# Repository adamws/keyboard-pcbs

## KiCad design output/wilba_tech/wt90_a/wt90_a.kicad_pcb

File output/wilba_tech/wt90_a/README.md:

## wilba_tech/wt90_a

[layout](wt90_a-kle.json) - [PCB](wt90_a.kicad_pcb)

{:loading="lazy"}

[Open in keyboard-layout-editor](http://www.keyboard-layout-editor.com/##@@_c=#777777;&=0,0&_x:0.25&c=#cccccc;&=0,1&=0,2&=0,3&=0,4&_x:0.25&c=#aaaaaa;&=0,5&=0,6&=0,7&=0,8&_x:0.25&c=#cccccc;&=0,9&=0,10&=0,11&=0,12&_x:0.25&c=#aaaaaa;&=0,13&_x:0.5;&=0,14&=0,15&=0,16&=0,17;&@_y:0.25&c=#cccccc;&=1,0&=1,1&=1,2&=1,3&=1,4&=1,5&=1,6&=1,7&=1,8&=1,9&=1,10&=1,11&=1,12&_c=#aaaaaa&w:2;&=1,13&_x:0.5;&=1,14&=1,15&=1,16&=1,17;&@_w:1.5;&=2,0&_c=#cccccc;&=2,1&=2,2&=2,3&=2,4&=2,5&=2,6&=2,7&=2,8&=2,9&=2,10&=2,11&=2,12&_w:1.5;&=2,13&_x:0.5;&=2,14&=2,15&=2,16&_c=#aaaaaa;&=2,17;&@_w:1.75;&=3,0&_c=#cccccc;&=3,1&=3,2&=3,3&=3,4&=3,5&=3,6&=3,7&=3,8&=3,9&=3,10&=3,11&_c=#777777&w:2.25;&=3,12&_x:0.5&c=#cccccc;&=3,14&=3,15&=3,16&_c=#aaaaaa;&=3,17;&@_w:2.25;&=4,0&_c=#cccccc;&=4,2&=4,3&=4,4&=4,5&=4,6&=4,7&=4,8&=4,9&=4,10&=4,11&_c=#aaaaaa&w:1.75;&=4,12&_x:1.5&c=#cccccc;&=4,14&=4,15&=4,16&_c=#777777&h:2;&=4,17;&@_x:14.25&y:-0.75&c=#cccccc;&=4,13;&@_y:-0.25&c=#aaaaaa&w:1.5;&=5,0&_w:1.5;&=5,1&_c=#cccccc&w:7;&=5,6&_c=#aaaaaa&w:1.5;&=5,10&_w:1.5;&=5,11&_x:3.5&c=#cccccc;&=5,15&=5,16;&@_x:13.25&y:-0.75;&=5,12&=5,13&=5,14)

{:loading="lazy"}

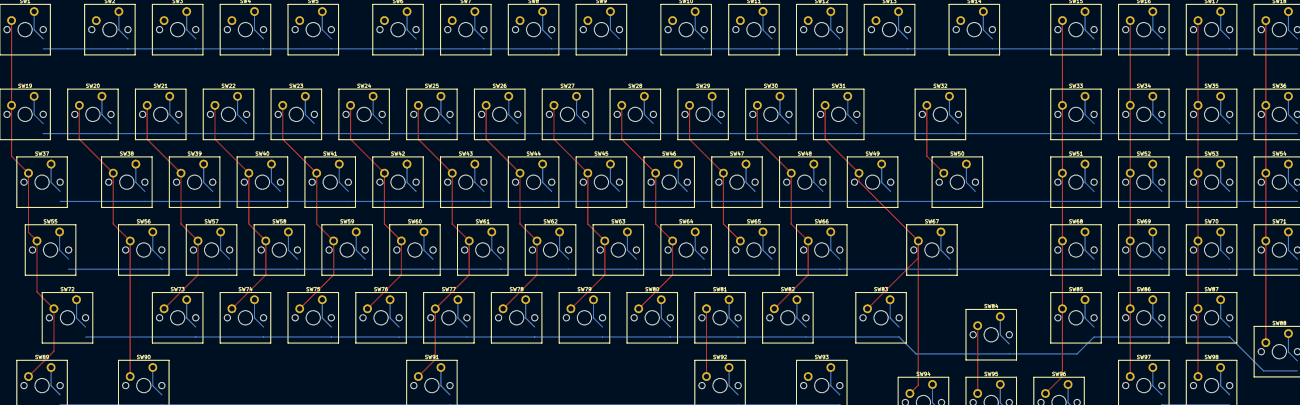
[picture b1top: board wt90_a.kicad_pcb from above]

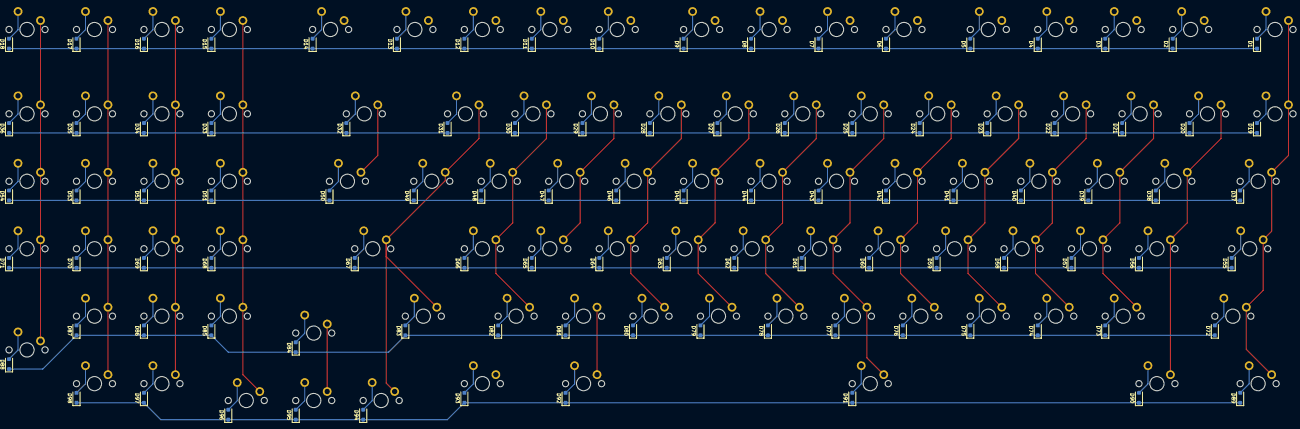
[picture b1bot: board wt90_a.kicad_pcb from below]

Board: 2 copper layers, 196 parts (98 on the bottom side), 122 nets.

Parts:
D1, D2, D3, D4, D5, D6, D7, D8, D9, D10, D11, D12, D13, D14, D15, D16, D17, D18, D19, D20, D21, D22, D23, D24, D25, D26, D27, D28, D29, D30, D31, D32, D33, D34, D35, D36, D37, D38, D39, D40, D41, D42, D43, D44, D45, D46, D47, D48, D49, D50, D51, D52, D53, D54, D55, D56, D57, D58, D59, D60, D61, D62, D63, D64, D65, D66, D67, D68, D69, D70, D71, D72, D73, D74, D75, D76, D77, D78, D79, D80, D81, D82, D83, D84, D85, D86, D87, D88, D89, D90, D91, D92, D93, D94, D95, D96, D97, D98: D_SOD-123F
SW1, SW2, SW3, SW4, SW5, SW6, SW7, SW8, SW9, SW10, SW11, SW12, SW13, SW14, SW15, SW16, SW17, SW18, SW19, SW20, SW21, SW22, SW23, SW24, SW25, SW26, SW27, SW28, SW29, SW30, SW31, SW32, SW33, SW34, SW35, SW36, SW37, SW38, SW39, SW40, SW41, SW42, SW43, SW44, SW45, SW46, SW47, SW48, SW49, SW50, SW51, SW52, SW53, SW54, SW55, SW56, SW57, SW58, SW59, SW60, SW61, SW62, SW63, SW64, SW65, SW66, SW67, SW68, SW69, SW70, SW71, SW72, SW73, SW74, SW75, SW76, SW77, SW78, SW79, SW80, SW81, SW82, SW83, SW84, SW85, SW86, SW87, SW88, SW89, SW90, SW91, SW92, SW93, SW94, SW95, SW96, SW97, SW98: SW_Cherry_MX_PCB_1.00u

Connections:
COL0: SW1.1, SW19.1, SW37.1, SW55.1, SW72.1, SW89.1
COL1: SW2.1, SW20.1, SW38.1, SW56.1, SW90.1
COL2: SW3.1, SW21.1, SW39.1, SW57.1, SW73.1
COL3: SW4.1, SW22.1, SW40.1, SW58.1, SW74.1
COL4: SW5.1, SW23.1, SW41.1, SW59.1, SW75.1
COL5: SW6.1, SW24.1, SW42.1, SW60.1, SW76.1
COL6: SW7.1, SW25.1, SW43.1, SW61.1, SW77.1, SW91.1
COL7: SW8.1, SW26.1, SW44.1, SW62.1, SW78.1
COL8: SW9.1, SW27.1, SW45.1, SW63.1, SW79.1
COL9: SW10.1, SW28.1, SW46.1, SW64.1, SW80.1
COL10: SW11.1, SW29.1, SW47.1, SW65.1, SW81.1, SW92.1
COL11: SW12.1, SW30.1, SW48.1, SW66.1, SW82.1, SW93.1
COL12: SW13.1, SW31.1, SW49.1, SW67.1, SW83.1, SW94.1
COL13: SW14.1, SW32.1, SW50.1, SW84.1, SW95.1
COL14: SW15.1, SW33.1, SW51.1, SW68.1, SW85.1, SW96.1
COL15: SW16.1, SW34.1, SW52.1, SW69.1, SW86.1, SW97.1
COL16: SW17.1, SW35.1, SW53.1, SW70.1, SW87.1, SW98.1
COL17: SW18.1, SW36.1, SW54.1, SW71.1, SW88.1
unnamed: D1.2, SW1.2
unnamed: D2.2, SW2.2
unnamed: D3.2, SW3.2
unnamed: D4.2, SW4.2
unnamed: D5.2, SW5.2
unnamed: D6.2, SW6.2
unnamed: D7.2, SW7.2
unnamed: D8.2, SW8.2
unnamed: D9.2, SW9.2
unnamed: D10.2, SW10.2
unnamed: D11.2, SW11.2
unnamed: D12.2, SW12.2
unnamed: D13.2, SW13.2
unnamed: D14.2, SW14.2
unnamed: D15.2, SW15.2
unnamed: D16.2, SW16.2
unnamed: D17.2, SW17.2
unnamed: D18.2, SW18.2
unnamed: D19.2, SW19.2
unnamed: D20.2, SW20.2
unnamed: D21.2, SW21.2
unnamed: D22.2, SW22.2
unnamed: D23.2, SW23.2
unnamed: D24.2, SW24.2
unnamed: D25.2, SW25.2
unnamed: D26.2, SW26.2
unnamed: D27.2, SW27.2
unnamed: D28.2, SW28.2
unnamed: D29.2, SW29.2
unnamed: D30.2, SW30.2
unnamed: D31.2, SW31.2
unnamed: D32.2, SW32.2
unnamed: D33.2, SW33.2
unnamed: D34.2, SW34.2
unnamed: D35.2, SW35.2
unnamed: D36.2, SW36.2
unnamed: D37.2, SW37.2
unnamed: D38.2, SW38.2
unnamed: D39.2, SW39.2
unnamed: D40.2, SW40.2
unnamed: D41.2, SW41.2
unnamed: D42.2, SW42.2
unnamed: D43.2, SW43.2
unnamed: D44.2, SW44.2
unnamed: D45.2, SW45.2
unnamed: D46.2, SW46.2
unnamed: D47.2, SW47.2
unnamed: D48.2, SW48.2
unnamed: D49.2, SW49.2
unnamed: D50.2, SW50.2
unnamed: D51.2, SW51.2
unnamed: D52.2, SW52.2
unnamed: D53.2, SW53.2
unnamed: D54.2, SW54.2
unnamed: D55.2, SW55.2
unnamed: D56.2, SW56.2
unnamed: D57.2, SW57.2
unnamed: D58.2, SW58.2
unnamed: D59.2, SW59.2
unnamed: D60.2, SW60.2
unnamed: D61.2, SW61.2
unnamed: D62.2, SW62.2
unnamed: D63.2, SW63.2
unnamed: D64.2, SW64.2
unnamed: D65.2, SW65.2
unnamed: D66.2, SW66.2
unnamed: D67.2, SW67.2
unnamed: D68.2, SW68.2
unnamed: D69.2, SW69.2
unnamed: D70.2, SW70.2
unnamed: D71.2, SW71.2
unnamed: D72.2, SW72.2
unnamed: D73.2, SW73.2
unnamed: D74.2, SW74.2
unnamed: D75.2, SW75.2
unnamed: D76.2, SW76.2
unnamed: D77.2, SW77.2
unnamed: D78.2, SW78.2
unnamed: D79.2, SW79.2
unnamed: D80.2, SW80.2
unnamed: D81.2, SW81.2
unnamed: D82.2, SW82.2
unnamed: D83.2, SW83.2
unnamed: D84.2, SW84.2
unnamed: D85.2, SW85.2
unnamed: D86.2, SW86.2
unnamed: D87.2, SW87.2
unnamed: D88.2, SW88.2
unnamed: D89.2, SW89.2
unnamed: D90.2, SW90.2
unnamed: D91.2, SW91.2
unnamed: D92.2, SW92.2
unnamed: D93.2, SW93.2
unnamed: D94.2, SW94.2
unnamed: D95.2, SW95.2
unnamed: D96.2, SW96.2
unnamed: D97.2, SW97.2
unnamed: D98.2, SW98.2
ROW0: D1.1, D2.1, D3.1, D4.1, D5.1, D6.1, D7.1, D8.1, D9.1, D10.1, D11.1, D12.1, D13.1, D14.1, D15.1, D16.1, D17.1, D18.1
ROW1: D19.1, D20.1, D21.1, D22.1, D23.1, D24.1, D25.1, D26.1, D27.1, D28.1, D29.1, D30.1, D31.1, D32.1, D33.1, D34.1, D35.1, D36.1
ROW2: D37.1, D38.1, D39.1, D40.1, D41.1, D42.1, D43.1, D44.1, D45.1, D46.1, D47.1, D48.1, D49.1, D50.1, D51.1, D52.1, D53.1, D54.1
ROW3: D55.1, D56.1, D57.1, D58.1, D59.1, D60.1, D61.1, D62.1, D63.1, D64.1, D65.1, D66.1, D67.1, D68.1, D69.1, D70.1, D71.1
ROW4: D72.1, D73.1, D74.1, D75.1, D76.1, D77.1, D78.1, D79.1, D80.1, D81.1, D82.1, D83.1, D84.1, D85.1, D86.1, D87.1, D88.1
ROW5: D89.1, D90.1, D91.1, D92.1, D93.1, D94.1, D95.1, D96.1, D97.1, D98.1

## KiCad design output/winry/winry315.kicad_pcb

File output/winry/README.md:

## winry/winry315

[layout](winry315-kle.json) - [PCB](winry315.kicad_pcb)

{:loading="lazy"}

[Open in keyboard-layout-editor](http://www.keyboard-layout-editor.com/##@@_d:true;&=0,0%0A%0A%0A0,0&_x:5&d:true;&=0,1%0A%0A%0A0,0;&@_x:2.75&y:-0.75&c=#777777&w:1.5&h:1.5;&=0,15%0A%0A%0A0,0;&@_x:0.75&y:-0.75;&=0,17%0A%0A%0A0,0&_x:3.5;&=0,16%0A%0A%0A0,0;&@_x:0.25&c=#aaaaaa;&=0,23%0A%0A%0A0,0&=0,22%0A%0A%0A0,0&_x:2.5;&=0,21%0A%0A%0A0,0&=0,20%0A%0A%0A0,0;&@_x:2.5&y:-0.75;&=0,19%0A%0A%0A0,0&=0,18%0A%0A%0A0,0;&@_x:1&y:0.25&c=#cccccc;&=0,0%0A%0A%0A0,0&=0,1%0A%0A%0A0,0&=0,2%0A%0A%0A0,0&=0,3%0A%0A%0A0,0&=0,4%0A%0A%0A0,0;&@_x:1;&=0,5%0A%0A%0A0,0&=0,6%0A%0A%0A0,0&=0,7%0A%0A%0A0,0&=0,8%0A%0A%0A0,0&=0,9%0A%0A%0A0,0;&@_x:1;&=0,10%0A%0A%0A0,0&=0,11%0A%0A%0A0,0&=0,12%0A%0A%0A0,0&=0,13%0A%0A%0A0,0&=0,14%0A%0A%0A0,0;&@_d:true;&=0,2%0A%0A%0A0,0&_x:5&d:true;&=0,3%0A%0A%0A0,0;&@_x:7&y:-7.0&d:true;&=0,2%0A%0A%0A0,2&_x:4&c=#777777;&=0,17%0A%0A%0A0,2&_c=#cccccc&d:true;&=0,0%0A%0A%0A0,2;&@_x:8;&=0,10%0A%0A%0A0,2&=0,5%0A%0A%0A0,2&=0,0%0A%0A%0A0,2&_x:0.5&c=#aaaaaa;&=0,23%0A%0A%0A0,2&=0,22%0A%0A%0A0,2;&@_x:8&c=#cccccc;&=0,11%0A%0A%0A0,2&=0,6%0A%0A%0A0,2&=0,1%0A%0A%0A0,2;&@_x:11.75&y:-0.75&c=#777777&w:1.5&h:1.5;&=0,15%0A%0A%0A0,2;&@_x:8&y:-0.25&c=#cccccc;&=0,12%0A%0A%0A0,2&=0,7%0A%0A%0A0,2&=0,2%0A%0A%0A0,2;&@_x:11.5&y:-0.25&c=#aaaaaa;&=0,19%0A%0A%0A0,2&=0,18%0A%0A%0A0,2;&@_x:8&y:-0.75&c=#cccccc;&=0,13%0A%0A%0A0,2&=0,8%0A%0A%0A0,2&=0,3%0A%0A%0A0,2;&@_x:8;&=0,14%0A%0A%0A0,2&=0,9%0A%0A%0A0,2&=0,4%0A%0A%0A0,2&_x:1&c=#777777;&=0,16%0A%0A%0A0,2;&@_x:7&c=#cccccc&d:true;&=0,3%0A%0A%0A0,2&_x:3.5&c=#aaaaaa;&=0,21%0A%0A%0A0,2&=0,20%0A%0A%0A0,2&_x:-0.5&c=#cccccc&d:true;&=0,1%0A%0A%0A0,2;&@_d:true;&=0,1%0A%0A%0A0,1&_c=#777777;&=0,16%0A%0A%0A0,1&_x:4&c=#cccccc&d:true;&=0,3%0A%0A%0A0,1&_d:true;&=0,3%0A%0A%0A0,3&_x:5&d:true;&=0,2%0A%0A%0A0,3;&@_x:0.5&c=#aaaaaa;&=0,21%0A%0A%0A0,1&=0,20%0A%0A%0A0,1&_x:0.5&c=#cccccc;&=0,4%0A%0A%0A0,1&=0,9%0A%0A%0A0,1&=0,14%0A%0A%0A0,1&_x:2.0;&=0,14%0A%0A%0A0,3&=0,13%0A%0A%0A0,3&=0,12%0A%0A%0A0,3&=0,11%0A%0A%0A0,3&=0,10%0A%0A%0A0,3;&@_x:3;&=0,3%0A%0A%0A0,1&=0,8%0A%0A%0A0,1&=0,13%0A%0A%0A0,1&_x:2;&=0,9%0A%0A%0A0,3&=0,8%0A%0A%0A0,3&=0,7%0A%0A%0A0,3&=0,6%0A%0A%0A0,3&=0,5%0A%0A%0A0,3;&@_x:0.75&y:-0.75&c=#777777&w:1.5&h:1.5;&=0,15%0A%0A%0A0,1;&@_x:3&y:-0.25&c=#cccccc;&=0,2%0A%0A%0A0,1&=0,7%0A%0A%0A0,1&=0,12%0A%0A%0A0,1&_x:2;&=0,4%0A%0A%0A0,3&=0,3%0A%0A%0A0,3&=0,2%0A%0A%0A0,3&=0,1%0A%0A%0A0,3&=0,0%0A%0A%0A0,3;&@_x:0.5&y:-0.25&c=#aaaaaa;&=0,19%0A%0A%0A0,1&=0,18%0A%0A%0A0,1;&@_x:3&y:-0.75&c=#cccccc;&=0,1%0A%0A%0A0,1&=0,6%0A%0A%0A0,1&=0,11%0A%0A%0A0,1;&@_x:9.75&y:-0.75&c=#777777&w:1.5&h:1.5;&=0,15%0A%0A%0A0,3;&@_x:7.75&y:-0.75;&=0,16%0A%0A%0A0,3&_x:3.5;&=0,17%0A%0A%0A0,3;&@_x:1&y:-0.5;&=0,17%0A%0A%0A0,1&_x:1&c=#cccccc;&=0,0%0A%0A%0A0,1&=0,5%0A%0A%0A0,1&=0,10%0A%0A%0A0,1;&@_x:7.25&y:-0.5&c=#aaaaaa;&=0,21%0A%0A%0A0,3&=0,20%0A%0A%0A0,3&_x:2.5;&=0,23%0A%0A%0A0,3&=0,22%0A%0A%0A0,3;&@_x:9.5&y:-0.75;&=0,19%0A%0A%0A0,3&=0,18%0A%0A%0A0,3;&@_y:-0.75&c=#cccccc&d:true;&=0,0%0A%0A%0A0,1&_x:-0.5&c=#aaaaaa;&=0,23%0A%0A%0A0,1&=0,22%0A%0A%0A0,1&_x:3.5&c=#cccccc&d:true;&=0,2%0A%0A%0A0,1&_d:true;&=0,1%0A%0A%0A0,3&_x:5.0&d:true;&=0,0%0A%0A%0A0,3)

{:loading="lazy"}

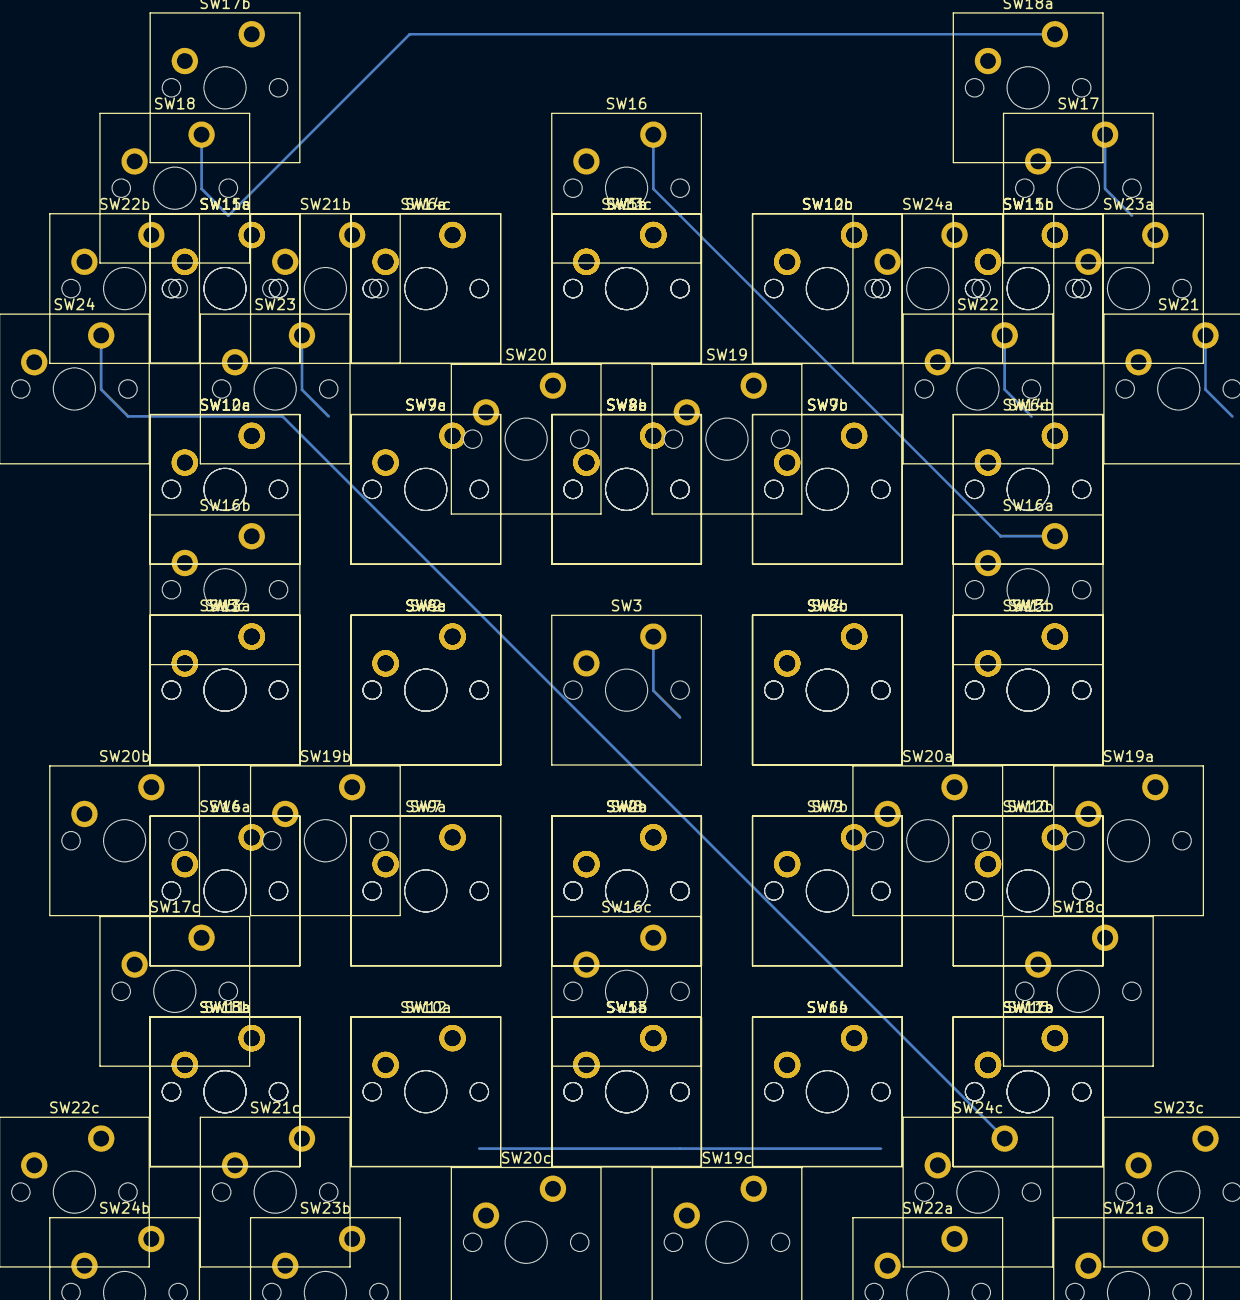
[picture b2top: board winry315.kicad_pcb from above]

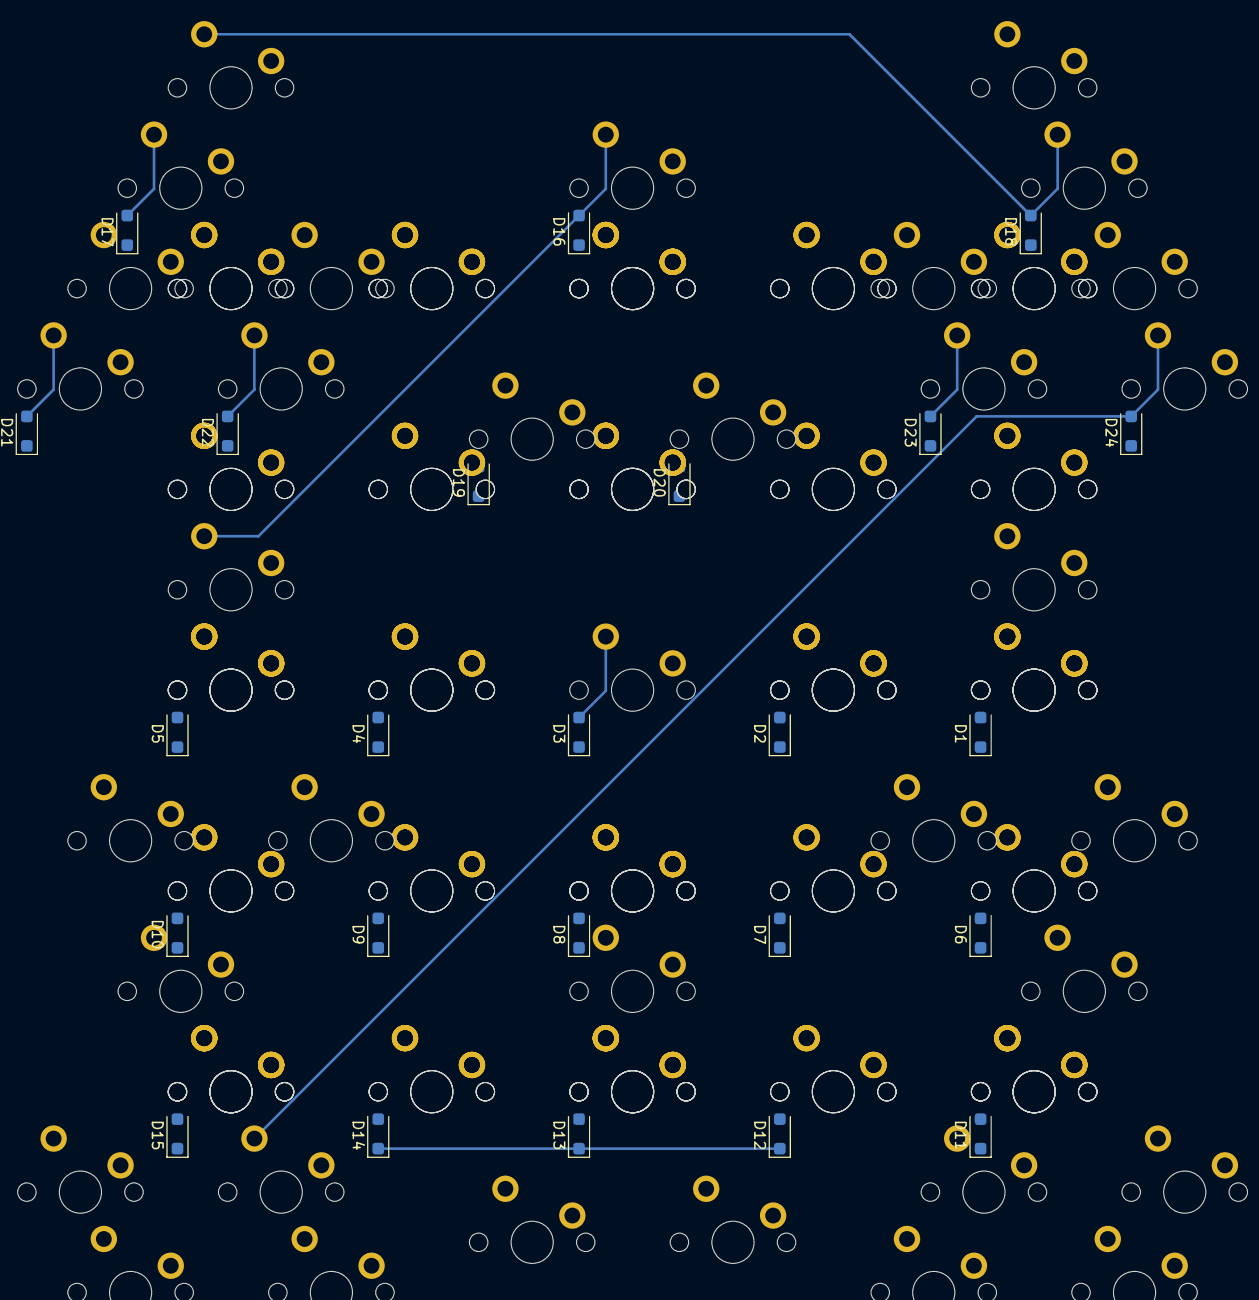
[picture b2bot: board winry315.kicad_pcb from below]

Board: 2 copper layers, 117 parts (24 on the bottom side), 48 nets.

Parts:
D1, D2, D3, D4, D5, D6, D7, D8, D9, D10, D11, D12, D13, D14, D15, D16, D17, D18, D19, D20, D21, D22, D23, D24: D_SOD-123F
SW1, SW1a, SW1b, SW1c, SW2, SW2a, SW2b, SW2c, SW3, SW4, SW4a, SW4b, SW4c, SW5, SW5a, SW5b, SW5c, SW6, SW6a, SW6b, SW6c, SW7, SW7a, SW7b, SW7c, SW8, SW8a, SW8b, SW8c, SW9, SW9a, SW9b, SW9c, SW10, SW10a, SW10b, SW10c, SW11, SW11a, SW11b, SW11c, SW12, SW12a, SW12b, SW12c, SW13, SW13a, SW13b, SW13c, SW14, SW14a, SW14b, SW14c, SW15, SW15a, SW15b, SW15c, SW16, SW16a, SW16b, SW16c, SW17, SW17a, SW17b, SW17c, SW18, SW18a, SW18b, SW18c, SW19, SW19a, SW19b, SW19c, SW20, SW20a, SW20b, SW20c, SW21, SW21a, SW21b, SW21c, SW22, SW22a, SW22b, SW22c, SW23, SW23a, SW23b, SW23c, SW24, SW24a, SW24b, SW24c: SW_Cherry_MX_PCB_1.00u

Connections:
COL0: SW1.1, SW1a.1, SW1b.1, SW1c.1
COL1: SW2.1, SW2a.1, SW2b.1, SW2c.1
COL3: SW4.1, SW4a.1, SW4b.1, SW4c.1
COL4: SW5.1, SW5a.1, SW5b.1, SW5c.1
COL5: SW6.1, SW6a.1, SW6b.1, SW6c.1
COL6: SW7.1, SW7a.1, SW7b.1, SW7c.1
COL7: SW8.1, SW8a.1, SW8b.1, SW8c.1
COL8: SW9.1, SW9a.1, SW9b.1, SW9c.1
COL9: SW10.1, SW10a.1, SW10b.1, SW10c.1
COL10: SW11.1, SW11a.1, SW11b.1, SW11c.1
COL11: SW12.1, SW12a.1, SW12b.1, SW12c.1
COL12: SW13.1, SW13a.1, SW13b.1, SW13c.1
COL13: SW14.1, SW14a.1, SW14b.1, SW14c.1
COL14: SW15.1, SW15a.1, SW15b.1, SW15c.1
COL15: SW16.1, SW16a.1, SW16b.1, SW16c.1
COL16: SW17.1, SW17a.1, SW17b.1, SW17c.1
COL17: SW18.1, SW18a.1, SW18b.1, SW18c.1
COL18: SW19.1, SW19a.1, SW19b.1, SW19c.1
COL19: SW20.1, SW20a.1, SW20b.1, SW20c.1
COL20: SW21.1, SW21a.1, SW21b.1, SW21c.1
COL21: SW22.1, SW22a.1, SW22b.1, SW22c.1
COL22: SW23.1, SW23a.1, SW23b.1, SW23c.1
COL23: SW24.1, SW24a.1, SW24b.1, SW24c.1
unnamed: D1.2, SW1.2, SW1a.2, SW1b.2, SW1c.2
unnamed: D2.2, SW2.2, SW2a.2, SW2b.2, SW2c.2
unnamed: D3.2, SW3.2
unnamed: D4.2, SW4.2, SW4a.2, SW4b.2, SW4c.2
unnamed: D5.2, SW5.2, SW5a.2, SW5b.2, SW5c.2
unnamed: D6.2, SW6.2, SW6a.2, SW6b.2, SW6c.2
unnamed: D7.2, SW7.2, SW7a.2, SW7b.2, SW7c.2
unnamed: D8.2, SW8.2, SW8a.2, SW8b.2, SW8c.2
unnamed: D9.2, SW9.2, SW9a.2, SW9b.2, SW9c.2
unnamed: D10.2, SW10.2, SW10a.2, SW10b.2, SW10c.2
unnamed: D11.2, SW11.2, SW11a.2, SW11b.2, SW11c.2
unnamed: D12.2, SW12.2, SW12a.2, SW12b.2, SW12c.2
unnamed: D13.2, SW13.2, SW13a.2, SW13b.2, SW13c.2
unnamed: D14.2, SW14.2, SW14a.2, SW14b.2, SW14c.2
unnamed: D15.2, SW15.2, SW15a.2, SW15b.2, SW15c.2
unnamed: D16.2, SW16.2, SW16a.2, SW16b.2, SW16c.2
unnamed: D17.2, SW17.2, SW17a.2, SW17b.2, SW17c.2
unnamed: D18.2, SW18.2, SW18a.2, SW18b.2, SW18c.2
unnamed: D19.2, SW19.2, SW19a.2, SW19b.2, SW19c.2
unnamed: D20.2, SW20.2, SW20a.2, SW20b.2, SW20c.2
unnamed: D21.2, SW21.2, SW21a.2, SW21b.2, SW21c.2
unnamed: D22.2, SW22.2, SW22a.2, SW22b.2, SW22c.2
unnamed: D23.2, SW23.2, SW23a.2, SW23b.2, SW23c.2
unnamed: D24.2, SW24.2, SW24a.2, SW24b.2, SW24c.2
ROW0: D1.1, D2.1, D3.1, D4.1, D5.1, D6.1, D7.1, D8.1, D9.1, D10.1, D11.1, D12.1, D13.1, D14.1, D15.1, D16.1, D17.1, D18.1, D19.1, D20.1, D21.1, D22.1, D23.1, D24.1
